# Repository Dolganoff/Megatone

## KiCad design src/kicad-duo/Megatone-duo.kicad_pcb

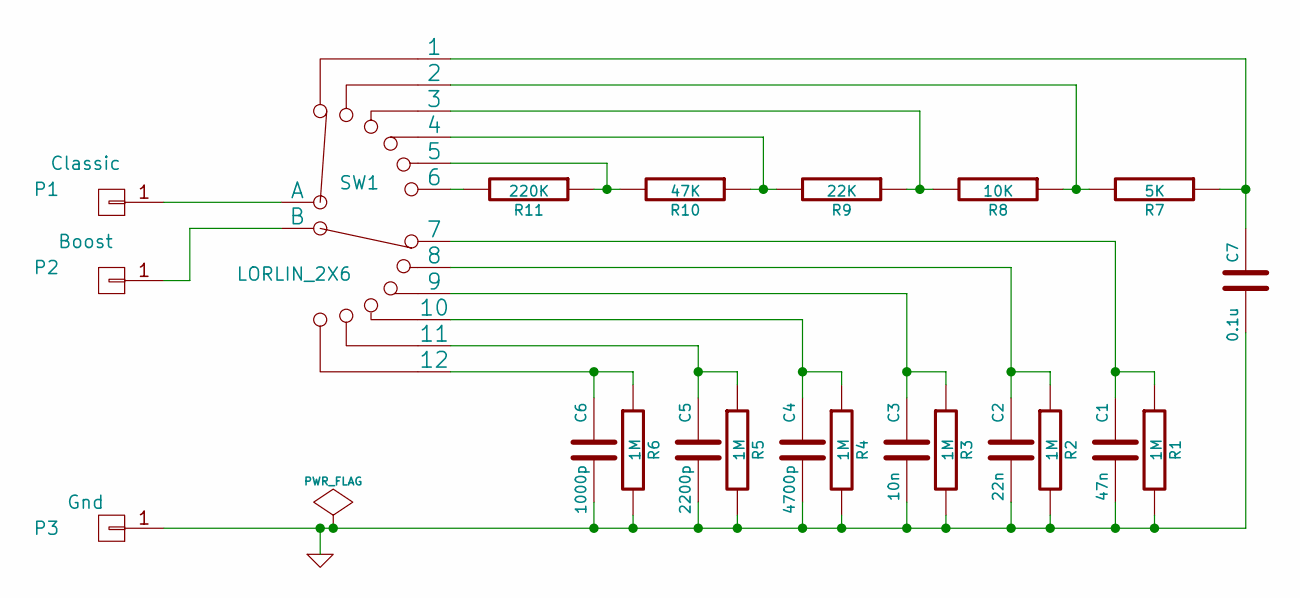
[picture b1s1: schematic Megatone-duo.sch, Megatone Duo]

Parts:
C1: 47n; SM0805
C2: 22n; SM0805
C3: 10n; SM0805
C4: 4700p; SM0805
C5: 2200p; SM0805
C6: 1000p; SM0805
C7: 0.1u; SM0805
P1: Classic; SIL-1
P2: Boost; SIL-1
P3: Gnd; SIL-1
R1, R2, R3, R4, R5, R6: 1M; SM0805
R7: 5K; SM0805
R8: 10K; SM0805
R9: 22K; SM0805
R10: 47K; SM0805
R11: 220K; SM0805
SW1: LORLIN_2X6; Lorlin_CK_2p6t

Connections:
GND: C1.2, C2.2, C3.2, C4.2, C5.2, C6.2, C7.1, P3.1, R1.2, R2.2, R3.2, R4.2, R5.2, R6.2
unnamed: C1.1, R1.1, SW1.7
unnamed: C2.1, R2.1, SW1.8
unnamed: C3.1, R3.1, SW1.9
unnamed: C4.1, R4.1, SW1.10
unnamed: C5.1, R5.1, SW1.11
unnamed: C6.1, R6.1, SW1.12
unnamed: C7.2, R7.1, SW1.1
unnamed: P1.1, SW1.A
unnamed: P2.1, SW1.B
unnamed: R7.2, R8.1, SW1.2
unnamed: R8.2, R9.1, SW1.3
unnamed: R9.2, R10.1, SW1.4
unnamed: R10.2, R11.1, SW1.5
unnamed: R11.2, SW1.6

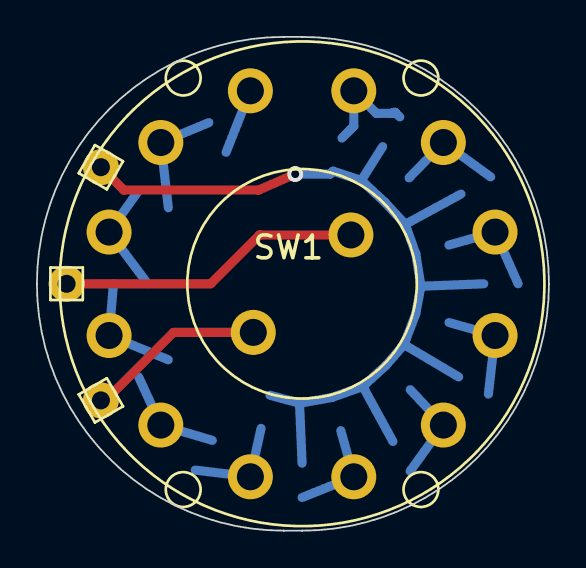
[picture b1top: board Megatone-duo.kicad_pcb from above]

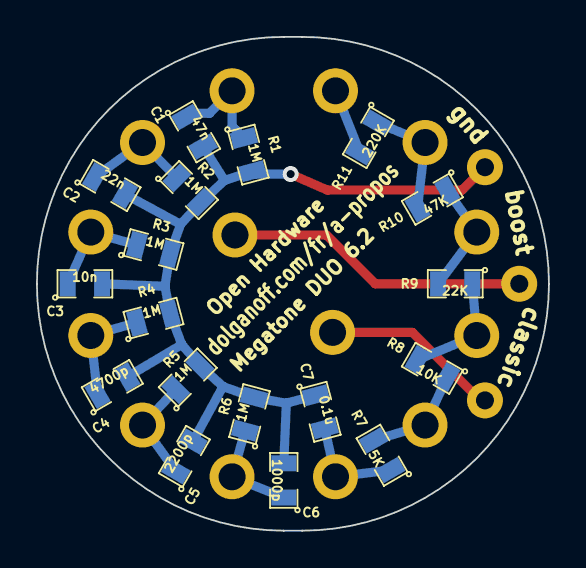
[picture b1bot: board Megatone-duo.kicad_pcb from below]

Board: 2 copper layers, 28.4 x 27.4 mm, 22 parts (18 on the bottom side), 15 nets.

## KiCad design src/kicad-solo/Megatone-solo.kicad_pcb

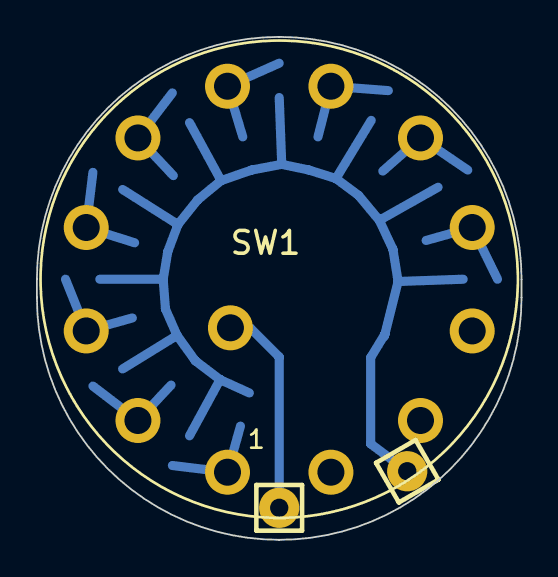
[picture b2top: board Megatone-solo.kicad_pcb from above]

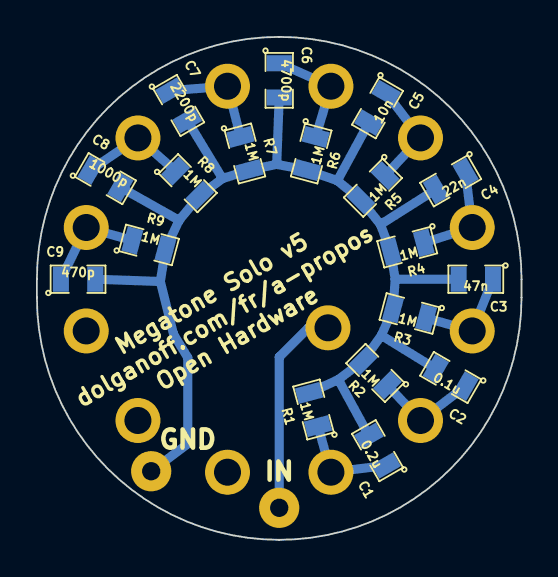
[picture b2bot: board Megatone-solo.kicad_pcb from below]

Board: 2 copper layers, 26.9 x 27.9 mm, 21 parts (18 on the bottom side), 11 nets.

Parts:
C1: 0.2u; SM0805
C2: 0.1u; SM0805
C3: 47n; SM0805
C4: 22n; SM0805
C5: 10n; SM0805
C6: 4700p; SM0805
C7: 2200p; SM0805
C8: 1000p; SM0805
C9: 470p; SM0805
P1, P2: CONN_01X01; Pin_Header_Straight_1x01
R1, R2, R3, R4, R5, R6, R7, R8, R9: 1M; SM0805
SW1: LORLIN_1X12; Lorlin_CK_1p12t

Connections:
GND: C1.2, C2.2, C3.2, C4.2, C5.2, C6.2, C7.2, C8.2, C9.2, P2.1, R1.2, R2.2, R3.2, R4.2, R5.2, R6.2, R7.2, R8.2, R9.2
unnamed: C1.1, R1.1, SW1.1
unnamed: C2.1, R2.1, SW1.2
unnamed: C3.1, R3.1, SW1.3
unnamed: C4.1, R4.1, SW1.4
unnamed: C5.1, R5.1, SW1.5
unnamed: C6.1, R6.1, SW1.6
unnamed: C7.1, R7.1, SW1.7
unnamed: C8.1, R8.1, SW1.8
unnamed: C9.1, R9.1, SW1.9
unnamed: P1.1, SW1.A

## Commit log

2014-10-21 rearranging folders
2014-10-21 2014-10-21
2014-10-21 2014-10-21--2
2014-10-22 2014-10-23
2014-10-23 2014-10-23 - updated solo and duo pcbs
2014-10-24 update pcbs and generate fab plots
2014-11-03 M. Duo: corrected wrong cap values on boost side
2014-11-03 Revert "M. Duo: corrected wrong cap values on boost side"
    This reverts commit b441f0806059993cadffced08bf4fcd550c3232b.
2014-11-03 updated documentaion graphics
2014-11-03 minor changes
2014-11-03 minor pcb mods
2015-01-01 moving output pins
2015-04-04 Turning output pins by 90°
2015-04-05 plots for v6.2

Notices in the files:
src/kicad-duo/Megatone-duo.sch:
Open Hardware, Licensed under CERN OHL v1.2
